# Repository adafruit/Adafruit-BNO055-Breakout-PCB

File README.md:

## Adafruit BNO055 Breakout PCB

<br/>
<br/>
Click here to purchase one from the Adafruit shop

PCB files for the BNO055 Breakout. Format is EagleCAD schematic and board layout
* https://www.adafruit.com/product/2472
* https://www.adafruit.com/product/4646

### Description

If you've ever ordered and wire up a 9-DOF sensor, chances are you've also realized the challenge of turning the sensor data from an accelerometer, gyroscope and magnetometer into actual "3D space orientation"! Orientation is a hard problem to solve. The sensor fusion algorithms (the secret sauce that blends accelerometer, magnetometer and gyroscope data into stable three-axis orientation output) can be mind-numbingly difficult to get right and implement on low cost real time systems.

Bosch is the first company to get this right by taking a MEMS accelerometer, magnetometer and gyroscope and putting them on a single die with a high speed ARM Cortex-M0 based processor to digest all the sensor data, abstract the sensor fusion and real time requirements away, and spit out data you can use in quaternions, Euler angles or vectors.

The new version of the board includes SparkFun qwiic compatible STEMMA QT connectors for the I2C bus so you don't even need to solder! Use a a plug-and-play STEMMA QT cable to get 9 DoF data ASAP.

Rather than spending weeks or months fiddling with algorithms of varying accuracy and complexity, you can have meaningful sensor data in minutes thanks to the BNO055 - a smart 9-DOF sensor that does the sensor fusion all on its own!  You can read the data right over I2C and Bob's yer uncle.

### License

Adafruit invests time and resources providing this open source design, please support Adafruit and open-source hardware by purchasing products from [Adafruit](https://www.adafruit.com)!

Designed by Limor Fried/Ladyada for Adafruit Industries.

Creative Commons Attribution/Share-Alike, all text above must be included in any redistribution. See license.txt for additional details.

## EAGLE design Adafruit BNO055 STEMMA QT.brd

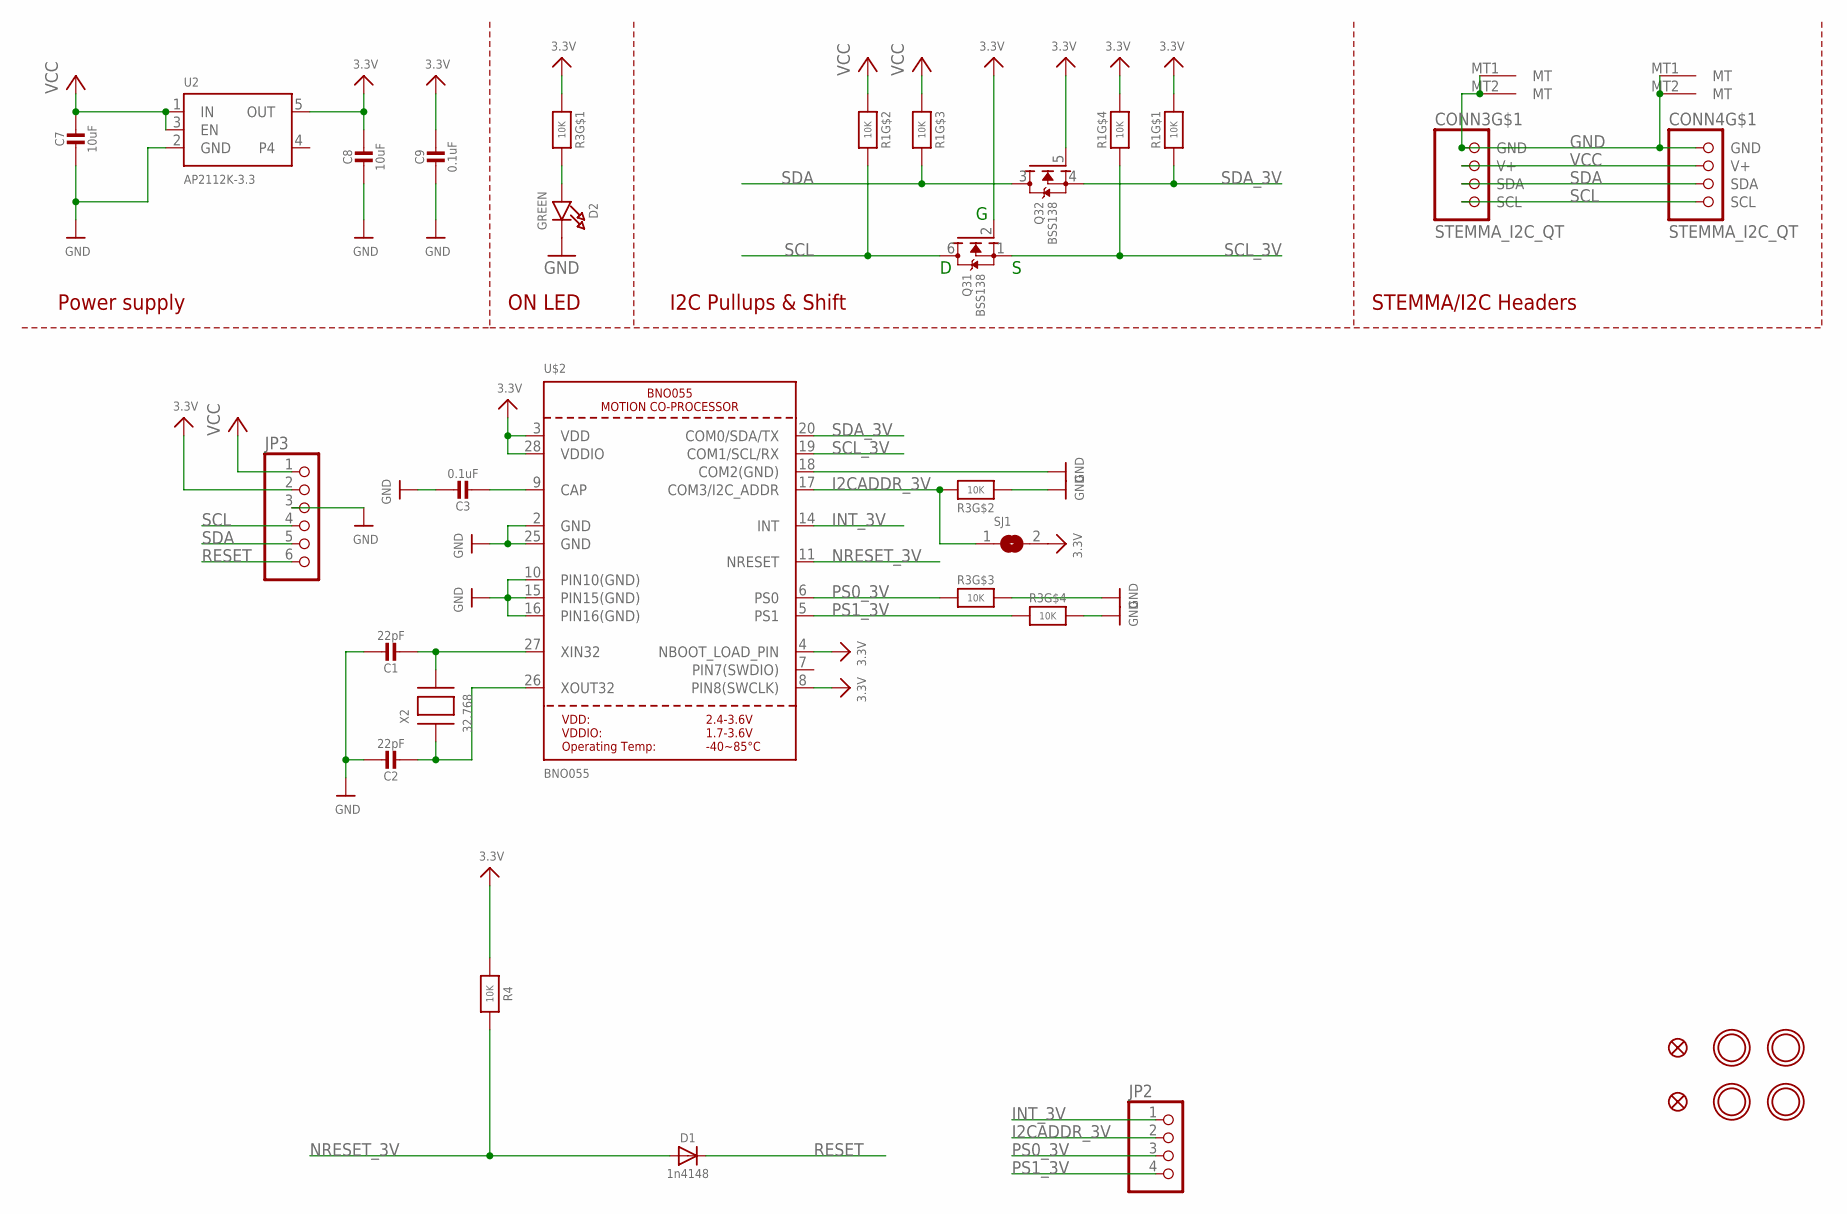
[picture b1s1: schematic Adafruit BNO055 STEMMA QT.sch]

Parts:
C1, C2: 22pF; 0603-NO
C3, C9: 0.1uF; 0603-NO
C7, C8: 10uF; 0805-NO
CONN3, CONN4: STEMMA_I2C_QT; JST_SH4
D1: 1n4148; SOD-323
D2: GREEN; CHIPLED_0603_NOOUTLINE
FID3, FID4: FIDUCIAL_1MM
JP2: HEADER-1X476MIL; 1X04_ROUND_76
JP3: HEADER-1X670MIL; 1X06_ROUND_70
Q3: BSS138; SOT363
R1, R3: 10K; RESPACK_4X0603
R4: 10K; 0603-NO
SJ1: SOLDERJUMPER; SOLDERJUMPER_ARROW_NOPASTE
U2: AP2112K-3.3; SOT23-5
U$2: BNO055
U$45, U$46, U$48, U$49: MOUNTINGHOLE2.5; MOUNTINGHOLE_2.5_PLATED
X2: 32.768; XTAL3215

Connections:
3.3V: C8.1, C9.1, JP3.2, Q3.2 (G), Q3.5 (G), R1.1, R1.4 (1), R3.1, R4.1, SJ1.2, U2.5 (OUT), U$2.3 (VDD), U$2.4 (NBOOT_LOAD_PIN), U$2.8 (PIN8(SWCLK)), U$2.28 (VDDIO)
GND: C1.1, C2.1, C3.1, C7.2, C8.2, C9.2, CONN3.1 (GND), CONN3.MT1 (MT), CONN3.MT2 (MT), CONN4.1 (GND), CONN4.MT1 (MT), CONN4.MT2 (MT), D2.C, JP3.3, R3.2 (1), R3.5 (2), R3.6 (2), U2.2 (GND), U$2.2 (GND), U$2.10 (PIN10(GND)), U$2.15 (PIN15(GND)), U$2.16 (PIN16(GND)), U$2.18 (COM2(GND)), U$2.25 (GND)
I2CADDR_3V: JP2.2, R3.7 (2), SJ1.1, U$2.17 (COM3/I2C_ADDR)
INT_3V: JP2.1, U$2.14 (INT)
unnamed: C1.2, U$2.27 (XIN32), X2.P$2
unnamed: C2.2, U$2.26 (XOUT32), X2.P$1
unnamed: C3.2, U$2.9 (CAP)
unnamed: D2.A, R3.8 (2)
NRESET_3V: D1.A, R4.2, U$2.11 (NRESET)
PS0_3V: JP2.3, R3.3 (1), U$2.6 (PS0)
PS1_3V: JP2.4, R3.4 (1), U$2.5 (PS1)
RESET: D1.C, JP3.6
SCL: CONN3.4 (SCL), CONN4.4 (SCL), JP3.4, Q3.6 (D), R1.7 (2)
SCL_3V: Q3.1 (S), R1.5 (2), U$2.19 (COM1/SCL/RX)
SDA: CONN3.3 (SDA), CONN4.3 (SDA), JP3.5, Q3.3 (D), R1.6 (2)
SDA_3V: Q3.4 (S), R1.8 (2), U$2.20 (COM0/SDA/TX)
VCC: C7.1, CONN3.2 (V+), CONN4.2 (V+), JP3.1, R1.2 (1), R1.3 (1), U2.1 (IN), U2.3 (EN)

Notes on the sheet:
I2C Pullups & Shift
STEMMA/I2C Headers
ON LED
Power supply

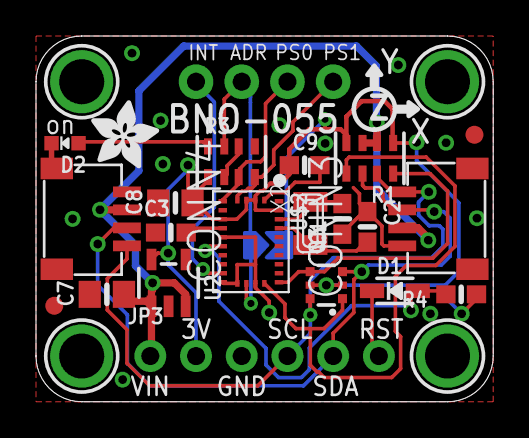
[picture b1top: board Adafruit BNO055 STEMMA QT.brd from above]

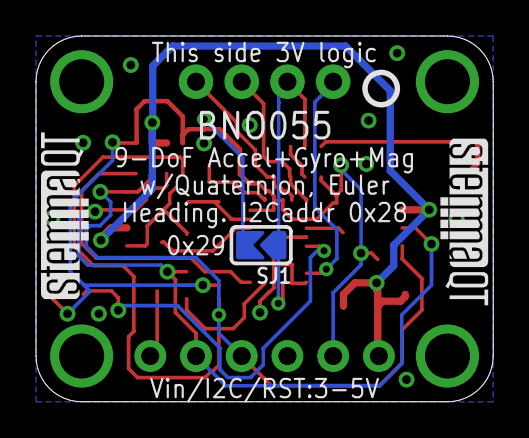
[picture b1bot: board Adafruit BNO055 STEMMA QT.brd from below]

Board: 2 copper layers, 25.4 x 20.3 mm, 30 parts (4 on the bottom side), 17 nets.

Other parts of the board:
U$51: ADAFRUIT_3.5MM
U$52: PCBFEAT-REV-040
U$53, U$54: STEMMAQT

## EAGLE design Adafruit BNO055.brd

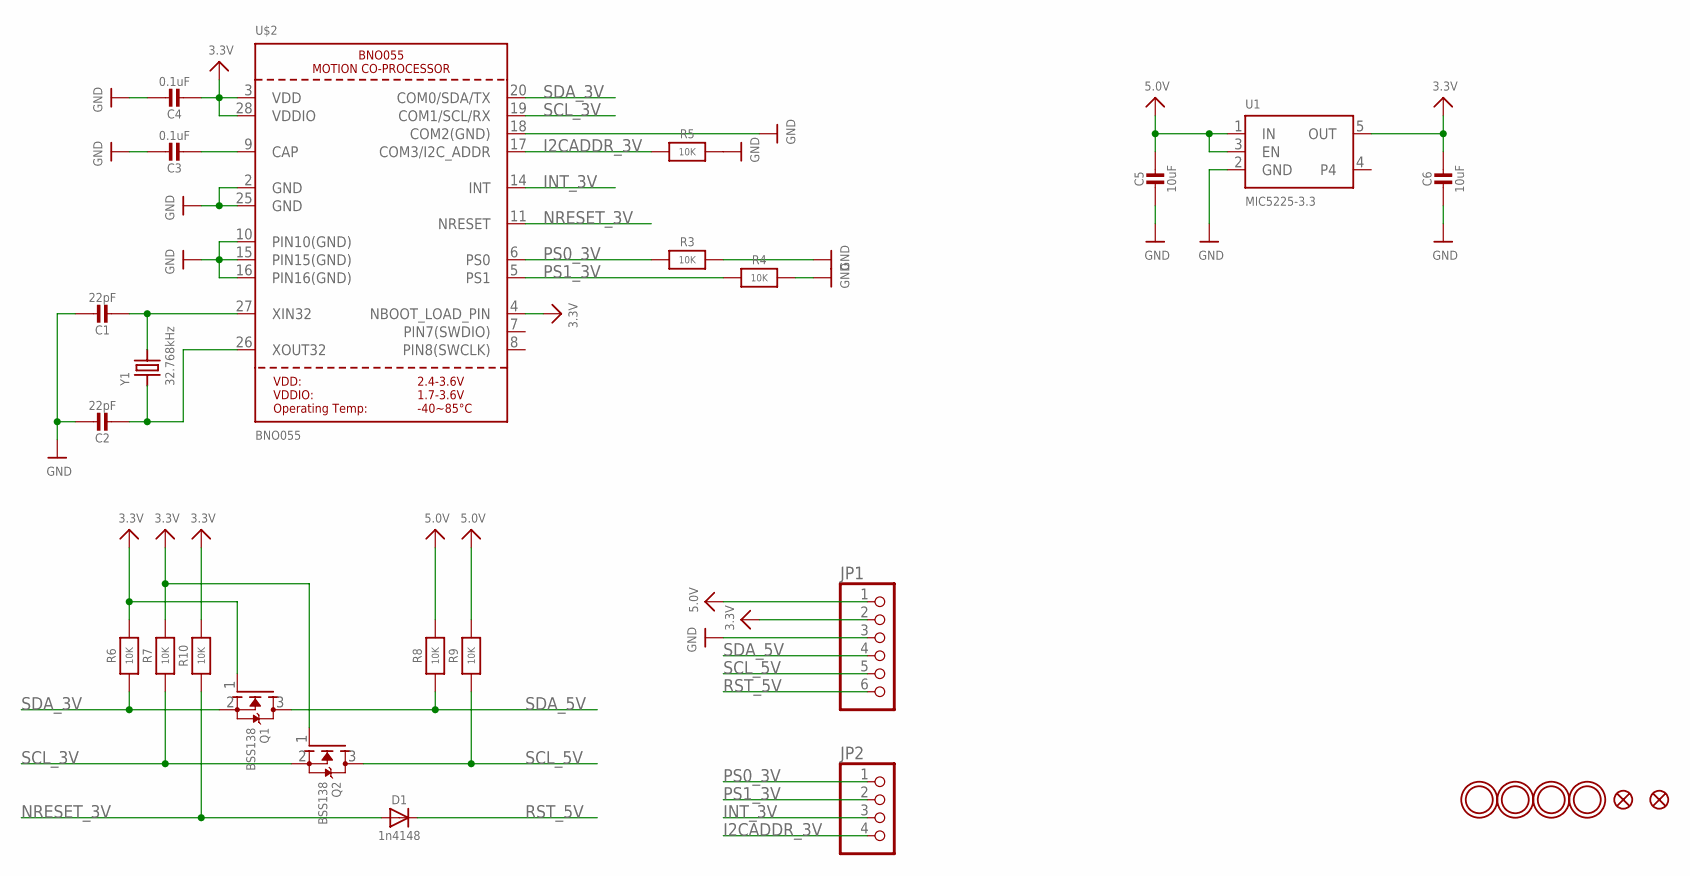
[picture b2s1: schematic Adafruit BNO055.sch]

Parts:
C1, C2: 22pF; 0805-NO
C3: 0.1uF; 0805-NO
C4: 0.1uF; 0805_10MGAP
C5: 10uF; 0805-NO
C6: 10uF; 0805_10MGAP
D1: 1n4148; SOD-323
FID1, FID2: FIDUCIAL""; FIDUCIAL_1MM
JP1: HEADER-1X676MIL; 1X06_ROUND_76
JP2: HEADER-1X476MIL; 1X04_ROUND_76
Q1, Q2: BSS138; SOT23-WIDE
R3, R4, R5, R6, R7, R10: 10K; 0805-NO
R8, R9: 10K; _0805MP
U1: MIC5225-3.3; SOT23-5
U$2: BNO055
U$29, U$30, U$31, U$32: MOUNTINGHOLE2.5_THICK; MOUNTINGHOLE_2.5_PLATED_THICK
Y1: 32.768kHz; CRYSTAL_8X3.8

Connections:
3.3V: C4.2, C6.1, JP1.2, Q1.1 (G), Q2.1 (G), R6.2, R7.2, R10.2, U1.5 (OUT), U$2.3 (VDD), U$2.4 (NBOOT_LOAD_PIN), U$2.28 (VDDIO)
5.0V: C5.1, JP1.1, R8.2, R9.2, U1.1 (IN), U1.3 (EN)
GND: C1.1, C2.1, C3.1, C4.1, C5.2, C6.2, JP1.3, R3.2, R4.2, R5.2, U1.2 (GND), U$2.2 (GND), U$2.10 (PIN10(GND)), U$2.15 (PIN15(GND)), U$2.16 (PIN16(GND)), U$2.18 (COM2(GND)), U$2.25 (GND)
I2CADDR_3V: JP2.4, R5.1, U$2.17 (COM3/I2C_ADDR)
INT_3V: JP2.3, U$2.14 (INT)
unnamed: C1.2, U$2.27 (XIN32), Y1.P$4 (2)
unnamed: C2.2, U$2.26 (XOUT32), Y1.P$1 (1)
unnamed: C3.2, U$2.9 (CAP)
NRESET_3V: D1.A, R10.1, U$2.11 (NRESET)
PS0_3V: JP2.1, R3.1, U$2.6 (PS0)
PS1_3V: JP2.2, R4.1, U$2.5 (PS1)
RST_5V: D1.C, JP1.6
SCL_3V: Q2.2 (S), R7.1, U$2.19 (COM1/SCL/RX)
SCL_5V: JP1.5, Q2.3 (D), R9.1
SDA_3V: Q1.2 (S), R6.1, U$2.20 (COM0/SDA/TX)
SDA_5V: JP1.4, Q1.3 (D), R8.1

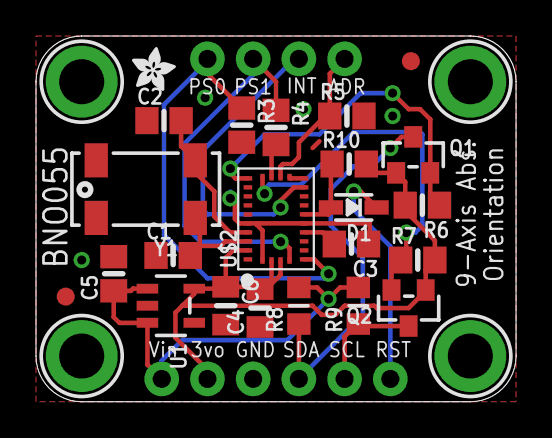
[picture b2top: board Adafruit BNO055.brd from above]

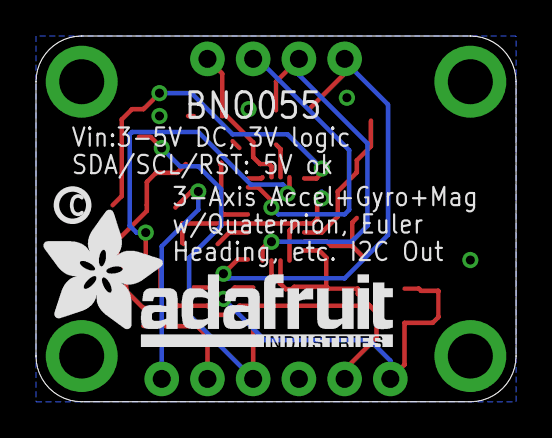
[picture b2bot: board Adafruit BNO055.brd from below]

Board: 2 copper layers, 26.7 x 20.3 mm, 31 parts (2 on the bottom side), 16 nets.

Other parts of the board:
U$3: PCBFEAT-REV-040
U$28: ADAFRUIT_TEXT_20MM
U$33: ADAFRUIT_2.5MM

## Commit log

2016-11-25 inti
2020-06-25 Add board files.
2020-06-25 Add image
2020-06-25 Update README.

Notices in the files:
parts and their libraries:
microbuilder: This work is placed in the public domain, and may be freely used for commercial and non-commercial work with the following conditions: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
